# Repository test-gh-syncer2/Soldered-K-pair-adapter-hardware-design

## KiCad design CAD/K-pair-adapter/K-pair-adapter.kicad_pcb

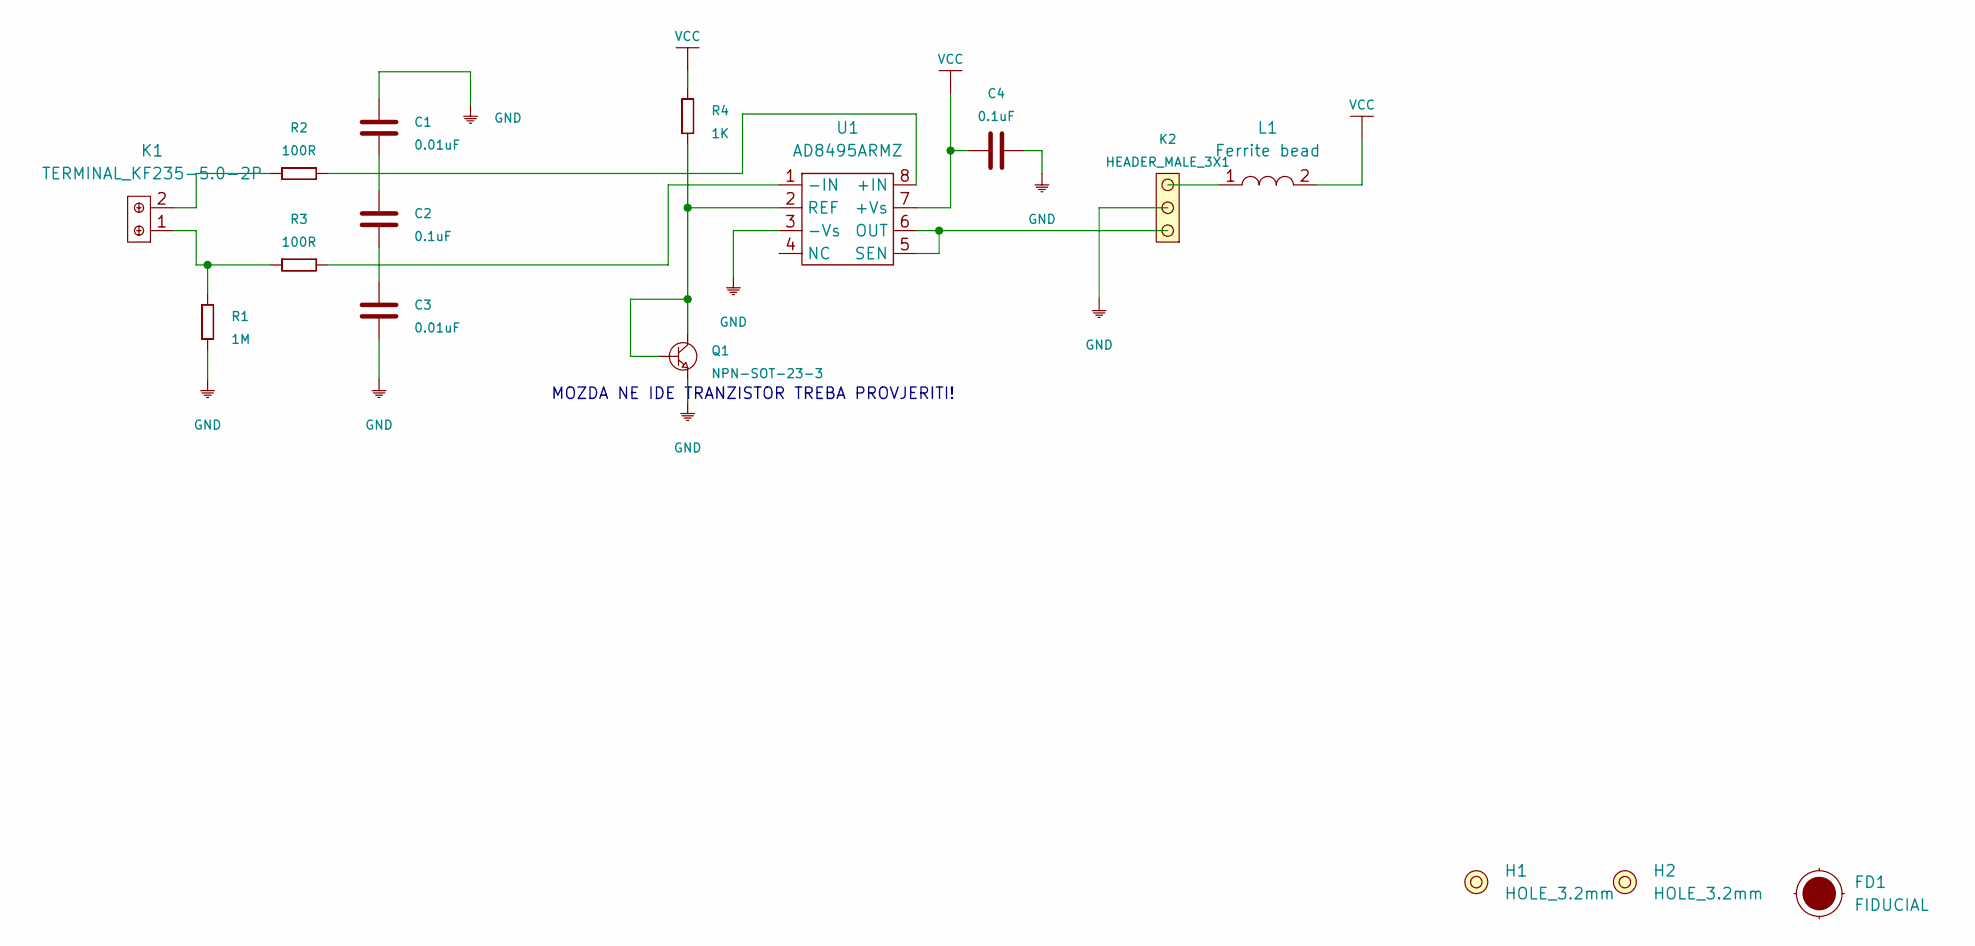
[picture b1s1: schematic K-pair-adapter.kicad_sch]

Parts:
C1, C3: 0.01uF; 0603C
C2, C4: 0.1uF; 0603C
FD1: FIDUCIAL; FIDUCIAL_23
H1, H2: HOLE_3.2mm
K1: TERMINAL_KF235-5.0-2P
K2: HEADER_MALE_3X1
L1: Ferrite bead; 0603L
Q1: NPN-SOT-23-3; SOT-23-3
R1: 1M; 0603R
R2, R3: 100R; 0603R
R4: 1K; 0603R
U1: AD8495ARMZ; TP4056M-MSOP8

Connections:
GND: C1.2, C3.1, C4.2, K2.2, Q1.2 (E), R1.1, U1.3 (-Vs)
unnamed: C1.1, C2.2
unnamed: C2.1, C3.2
unnamed: K1.1, R1.2, R3.1
unnamed: K1.2, R2.1
unnamed: K2.1, U1.5 (SEN), U1.6 (OUT)
unnamed: K2.3, L1.1
unnamed: Q1.1 (B), Q1.3 (C), R4.1, U1.2 (REF)
unnamed: R2.2, U1.8 (+IN)
unnamed: R3.2, U1.1 (-IN)
VCC: C4.1, L1.2, R4.2, U1.7 (+Vs)

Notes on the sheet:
MOZDA NE IDE TRANZISTOR TREBA PROVJERITI!

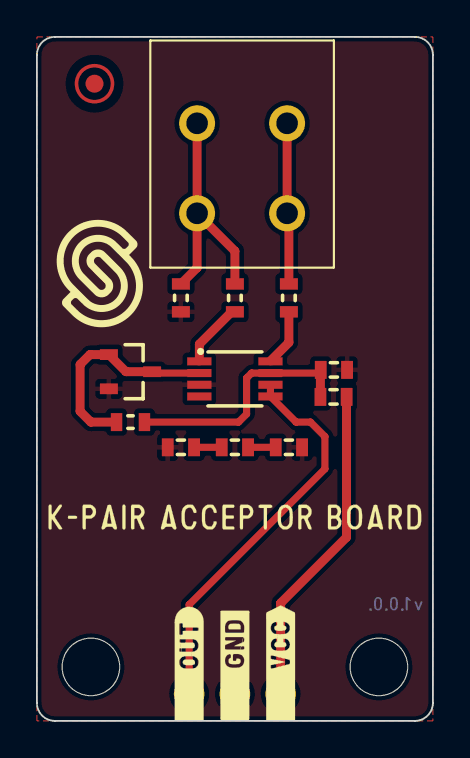
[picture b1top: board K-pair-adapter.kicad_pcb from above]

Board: 2 copper layers, 22.0 x 38.0 mm, 17 parts (1 on the bottom side), 11 nets.

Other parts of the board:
Ref**: Val**; Version1.0.0.

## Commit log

2021-09-23 Syncing to git
2021-09-23 Updating open source files.
